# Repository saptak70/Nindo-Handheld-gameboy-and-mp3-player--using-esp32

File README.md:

# RetroHand — ESP32-S3 Retro Gaming + BT Audio Handheld

A custom handheld device built from scratch — PCB, firmware, 
and enclosure. Plays NES/DOOM, streams audio to BT headphones.

## Features
- ESP32-S3-WROOM-1 N8R8 (dual core, BT5, 8MB PSRAM)
- ST7789V3 1.69" 240×280 SPI display
- PCM5102A I2S DAC + 3.5mm jack + BT A2DP
- MicroSD for ROMs and music
- LiPo battery with TP4056 charging + DW01A protection
- Custom KiCad PCB + 3D printed enclosure

## Photos
[photos here]

## Hardware
[link to schematic PDF]
[link to BOM]

## Build Guide
[step by step]

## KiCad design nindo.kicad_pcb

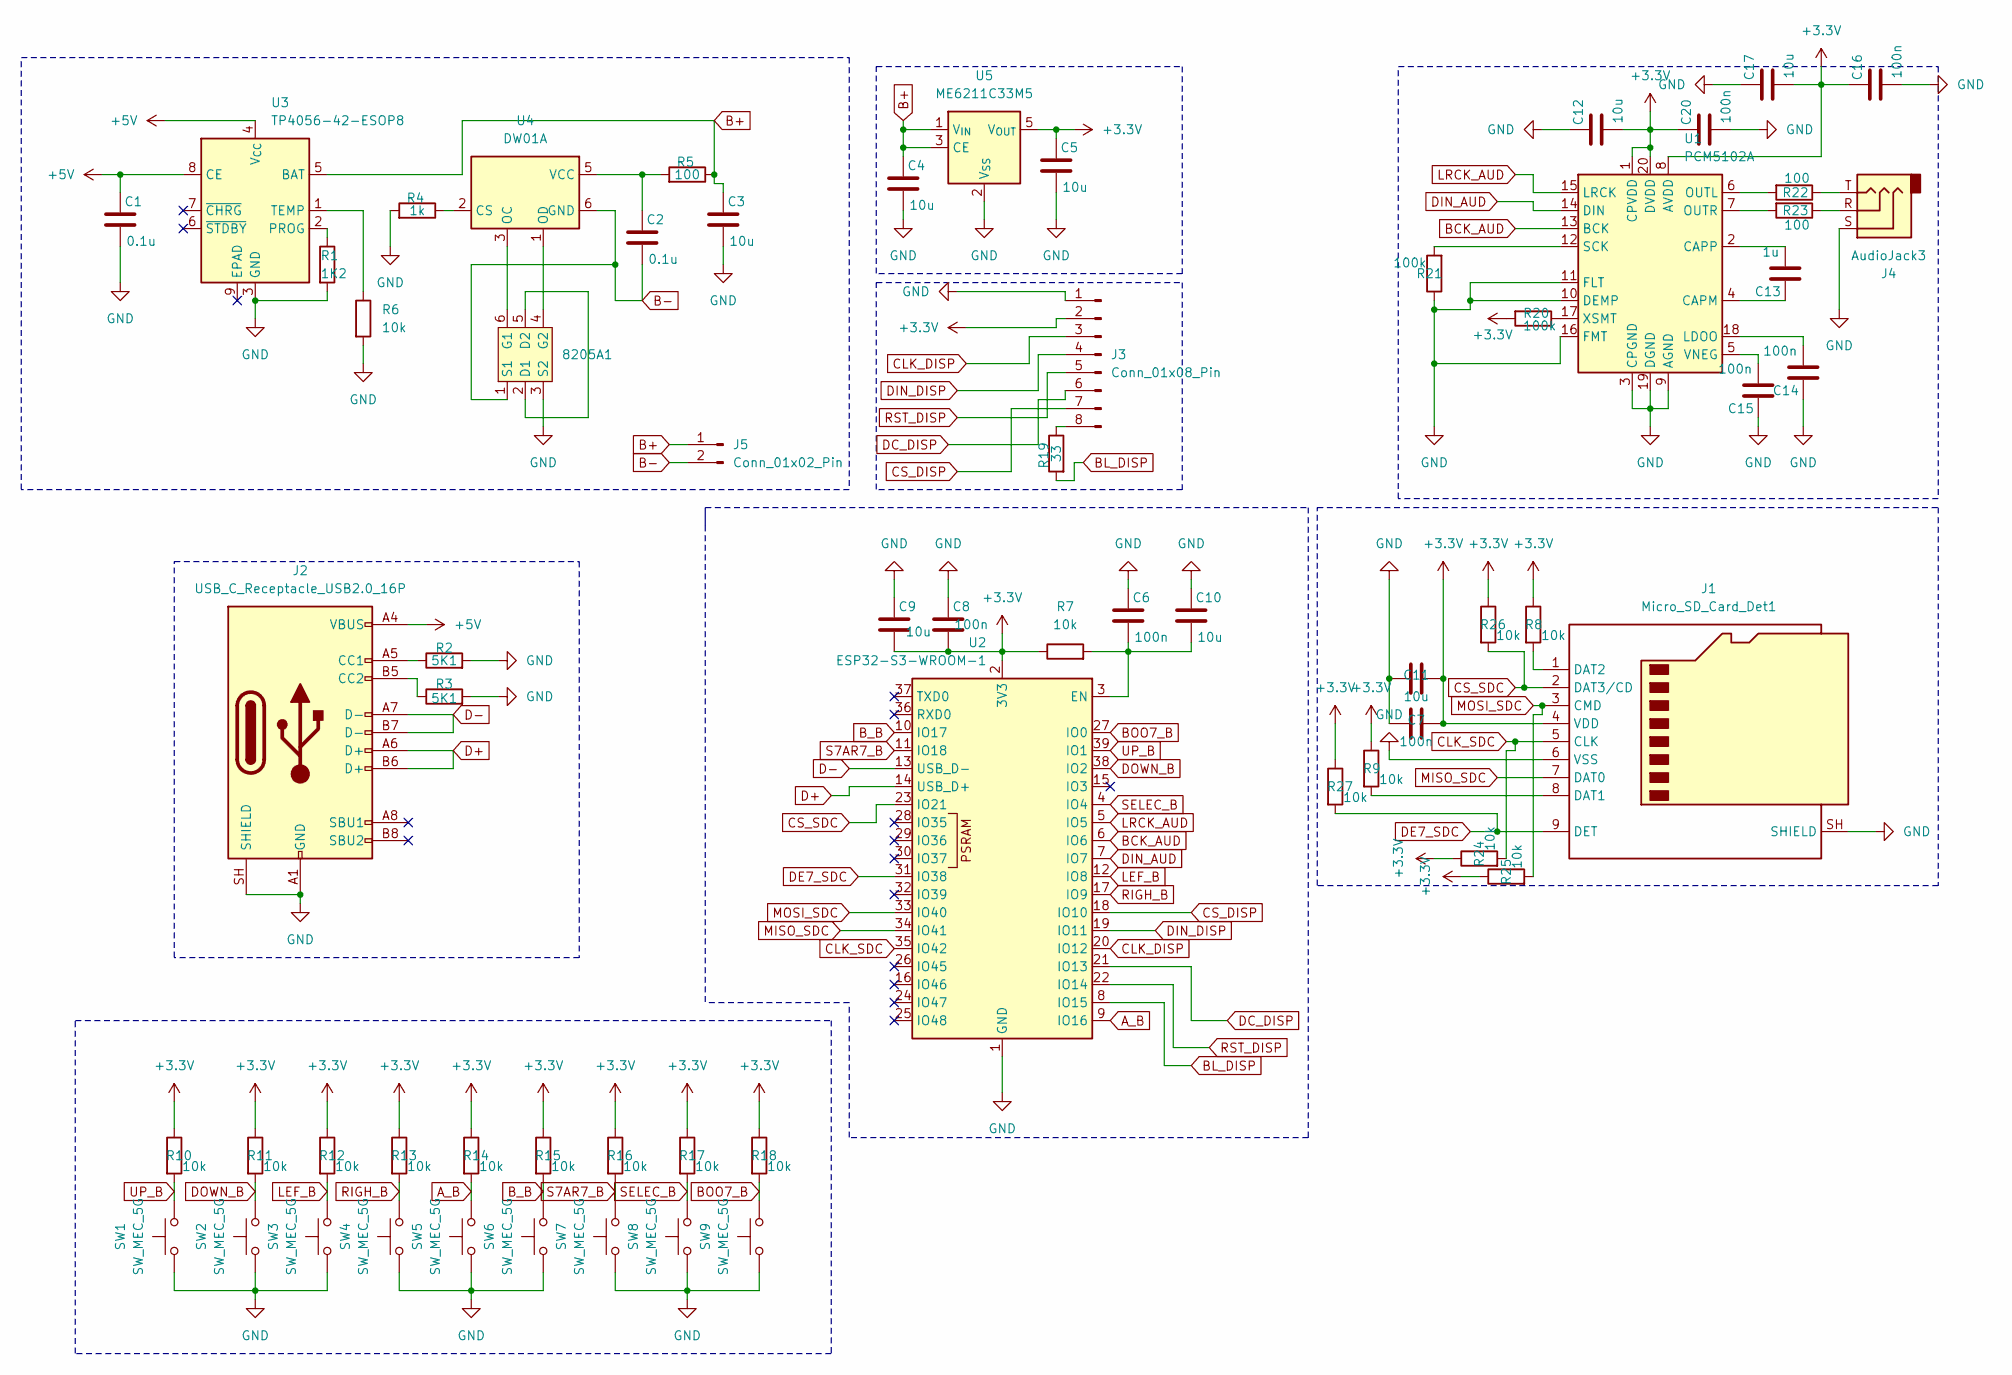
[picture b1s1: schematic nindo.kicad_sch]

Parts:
8205A1: SOT-23-6
C1, C2: 0.1u; C_1206_3216Metric_Pad1.33x1.80mm_HandSolder
C3, C4, C5, C9, C10, C11, C12, C17: 10u; C_1206_3216Metric_Pad1.33x1.80mm_HandSolder
C6, C7, C8, C14, C15, C16, C20: 100n; C_1206_3216Metric_Pad1.33x1.80mm_HandSolder
C13: 1u; C_1206_3216Metric_Pad1.33x1.80mm_HandSolder
J1: Micro_SD_Card_Det1; microSD_HC_Hirose_DM3AT-SF-PEJM5
J2: USB_C_Receptacle_USB2.0_16P; USB_C_Receptacle_G-Switch_GT-USB-7010ASV
J3: Conn_01x08_Pin; Harwin_M20-89008xx_1x08_P2.54mm_Horizontal
J4: AudioJack3; Jack_3.5mm_CUI_SJ1-3523N_Horizontal
J5: Conn_01x02_Pin; JWT_A3963_1x02_P3.96mm_Vertical
R1: 1K2; R_1206_3216Metric_Pad1.30x1.75mm_HandSolder
R2, R3: 5K1; R_1206_3216Metric_Pad1.30x1.75mm_HandSolder
R4: 1k; R_1206_3216Metric_Pad1.30x1.75mm_HandSolder
R5, R22, R23: 100; R_1206_3216Metric_Pad1.30x1.75mm_HandSolder
R6, R7, R8, R9, R10, R11, R12, R13, R14, R15, R16, R17, R18, R24, R25, R26, R27: 10k; R_1206_3216Metric_Pad1.30x1.75mm_HandSolder
R19: 33; R_1206_3216Metric_Pad1.30x1.75mm_HandSolder
R20, R21: 100k; R_1206_3216Metric_Pad1.30x1.75mm_HandSolder
SW1, SW2, SW3, SW4, SW5, SW6, SW7, SW8, SW9: SW_MEC_5G; SW_MEC_5GSH9
U1: PCM5102A; TSSOP-20_4.4x6.5mm_P0.65mm
U2: ESP32-S3-WROOM-1
U3: TP4056-42-ESOP8; SOIC-8-1EP_3.9x4.9mm_P1.27mm_EP2.41x3.3mm_ThermalVias
U4: DW01A; SOT-23-6
U5: ME6211C33M5; SOT-23-5

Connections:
+3.3V: C5.1, C7.2, C8.2, C9.2, C11.2, C12.2, C16.1, C17.2, C20.1, J1.4 (VDD), J3.2, R7.1, R8.1, R9.1, R10.1, R11.1, R12.1, R13.1, R14.1, R15.1, R16.1, R17.1, R18.1, R20.2, R24.1, R25.1, R26.1, R27.1, U1.1 (CPVDD), U1.8 (AVDD), U1.20 (DVDD), U2.2 (3V3), U5.5 (V_{OUT})
+5V: C1.1, J2.A4 (VBUS), J2.A9 (VBUS), J2.B4 (VBUS), J2.B9 (VBUS), U3.4 (V_{CC}), U3.8 (CE)
A_B: R14.2, SW5.3 (B), SW5.4 (B), U2.9 (IO16)
B+: C3.1, C4.1, J5.1, R5.1, U3.5 (BAT), U5.1 (V_{IN}), U5.3 (CE)
B-: 8205A1.1 (S1), C2.2, J5.2, U4.6 (GND)
BCK_AUD: U1.13 (BCK), U2.6 (IO6)
BL_DISP: R19.2, U2.8 (IO15)
BOO7_B: R18.2, SW9.3 (B), SW9.4 (B), U2.27 (IO0)
B_B: R15.2, SW6.3 (B), SW6.4 (B), U2.10 (IO17)
CLK_DISP: J3.3, U2.20 (IO12)
CLK_SDC: J1.5 (CLK), R24.2, U2.35 (IO42)
CS_DISP: J3.7, U2.18 (IO10)
CS_SDC: J1.2 (DAT3/CD), R26.2, U2.23 (IO21)
D+: J2.A6 (D+), J2.B6 (D+), U2.14 (USB_D+)
D-: J2.A7 (D-), J2.B7 (D-), U2.13 (USB_D-)
DC_DISP: J3.6, U2.21 (IO13)
DE7_SDC: J1.9 (DET), R27.2, U2.31 (IO38)
DIN_AUD: U1.14 (DIN), U2.7 (IO7)
DIN_DISP: J3.4, U2.19 (IO11)
DOWN_B: R11.2, SW2.3 (B), SW2.4 (B), U2.38 (IO2)
GND: 8205A1.3 (S2), C1.2, C3.2, C4.2, C5.2, C6.1, C7.1, C8.1, C9.1, C10.1, C11.1, C12.1, C14.1, C15.1, C16.2, C17.1, C20.2, J1.6 (VSS), J1.SH (SHIELD), J2.A1 (GND), J2.A12 (GND), J2.B1 (GND), J2.B12 (GND), J2.SH (SHIELD), J3.1, J4.S, R1.2, R2.2, R3.2, R4.2, R6.2, R21.1, SW1.1 (A), SW1.2 (A), SW2.1 (A), SW2.2 (A), SW3.1 (A), SW3.2 (A), SW4.1 (A), SW4.2 (A), SW5.1 (A), SW5.2 (A), SW6.1 (A), SW6.2 (A), SW7.1 (A), SW7.2 (A), SW8.1 (A), SW8.2 (A), SW9.1 (A), SW9.2 (A), U1.3 (CPGND), U1.9 (AGND), U1.10 (DEMP), U1.11 (FLT), U1.16 (FMT), U1.19 (DGND), U2.1 (GND), U2.40 (GND), U2.41 (GND), U3.3 (GND), U5.2 (V_{SS})
LEF_B: R12.2, SW3.3 (B), SW3.4 (B), U2.12 (IO8)
LRCK_AUD: U1.15 (LRCK), U2.5 (IO5)
MISO_SDC: J1.7 (DAT0), U2.34 (IO41)
MOSI_SDC: J1.3 (CMD), R25.2, U2.33 (IO40)
unnamed: 8205A1.2 (D1), 8205A1.5 (D2)
unnamed: 8205A1.6 (G1), U4.3 (OC)
unnamed: 8205A1.4 (G2), U4.1 (OD)
unnamed: J1.8 (DAT1), R9.2
unnamed: J1.1 (DAT2), R8.2
unnamed: J2.A5 (CC1), R2.1
unnamed: J2.B5 (CC2), R3.1
unnamed: J3.8, R19.1
unnamed: J4.R, R23.1
unnamed: J4.T, R22.1
unnamed: C13.1, U1.4 (CAPM)
unnamed: C13.2, U1.2 (CAPP)
unnamed: C14.2, U1.18 (LDOO)
unnamed: R22.2, U1.6 (OUTL)
unnamed: R23.2, U1.7 (OUTR)
unnamed: R21.2, U1.12 (SCK)
unnamed: C15.2, U1.5 (VNEG)
unnamed: R20.1, U1.17 (XSMT)
unnamed: C6.2, C10.2, R7.2, U2.3 (EN)
unnamed: R1.1, U3.2 (PROG)
unnamed: R6.1, U3.1 (TEMP)
unnamed: R4.1, U4.2 (CS)
unnamed: C2.1, R5.2, U4.5 (VCC)
RIGH_B: R13.2, SW4.3 (B), SW4.4 (B), U2.17 (IO9)
RST_DISP: J3.5, U2.22 (IO14)
S7AR7_B: R16.2, SW7.3 (B), SW7.4 (B), U2.11 (IO18)
SELEC_B: R17.2, SW8.3 (B), SW8.4 (B), U2.4 (IO4)
UP_B: R10.2, SW1.3 (B), SW1.4 (B), U2.39 (IO1)

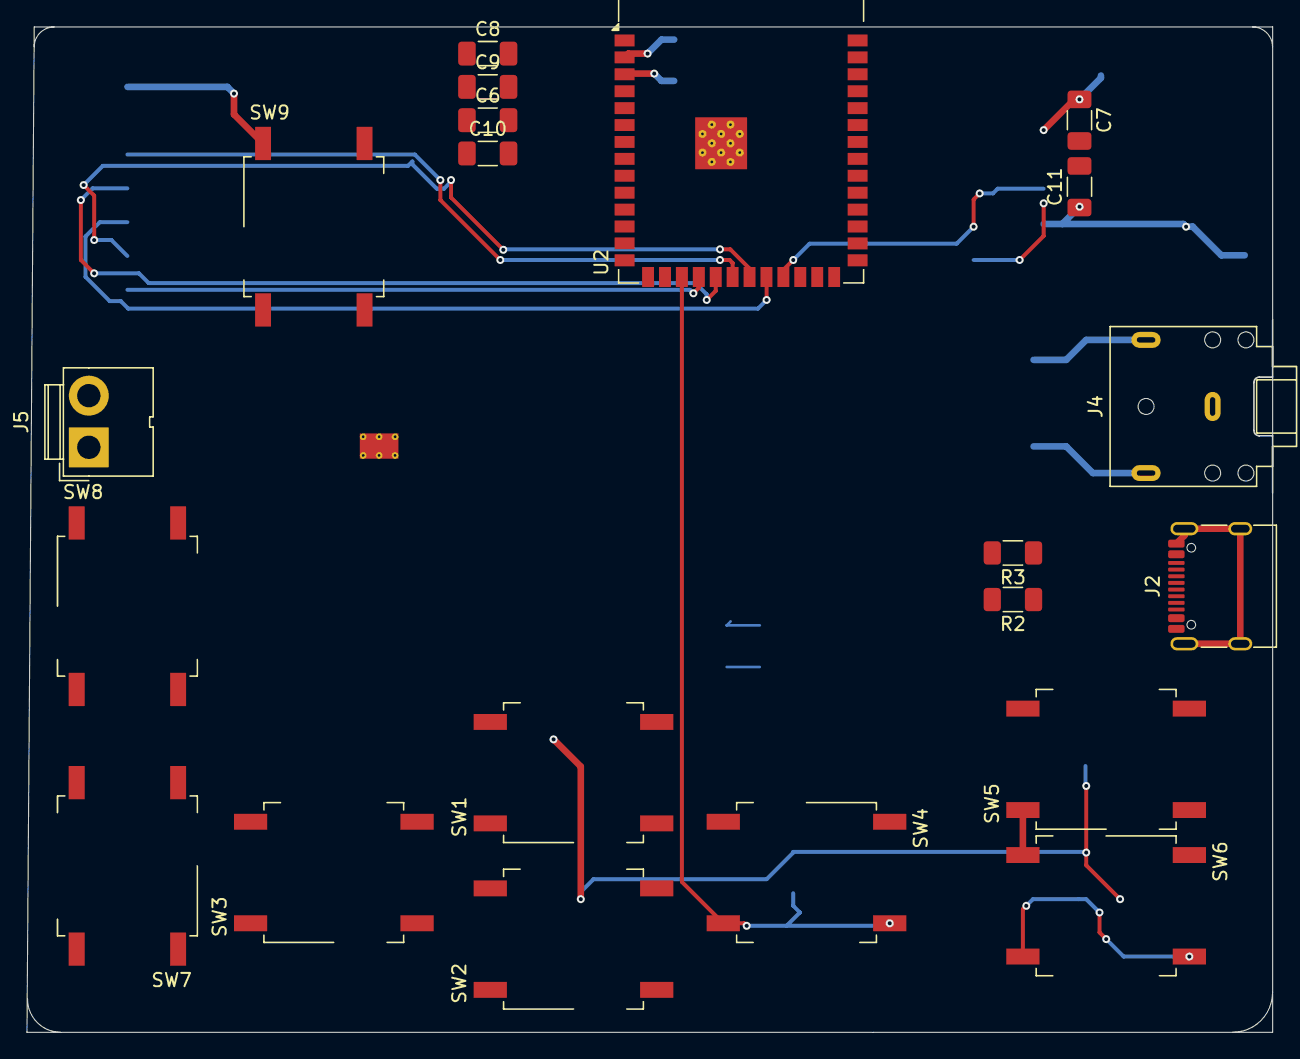
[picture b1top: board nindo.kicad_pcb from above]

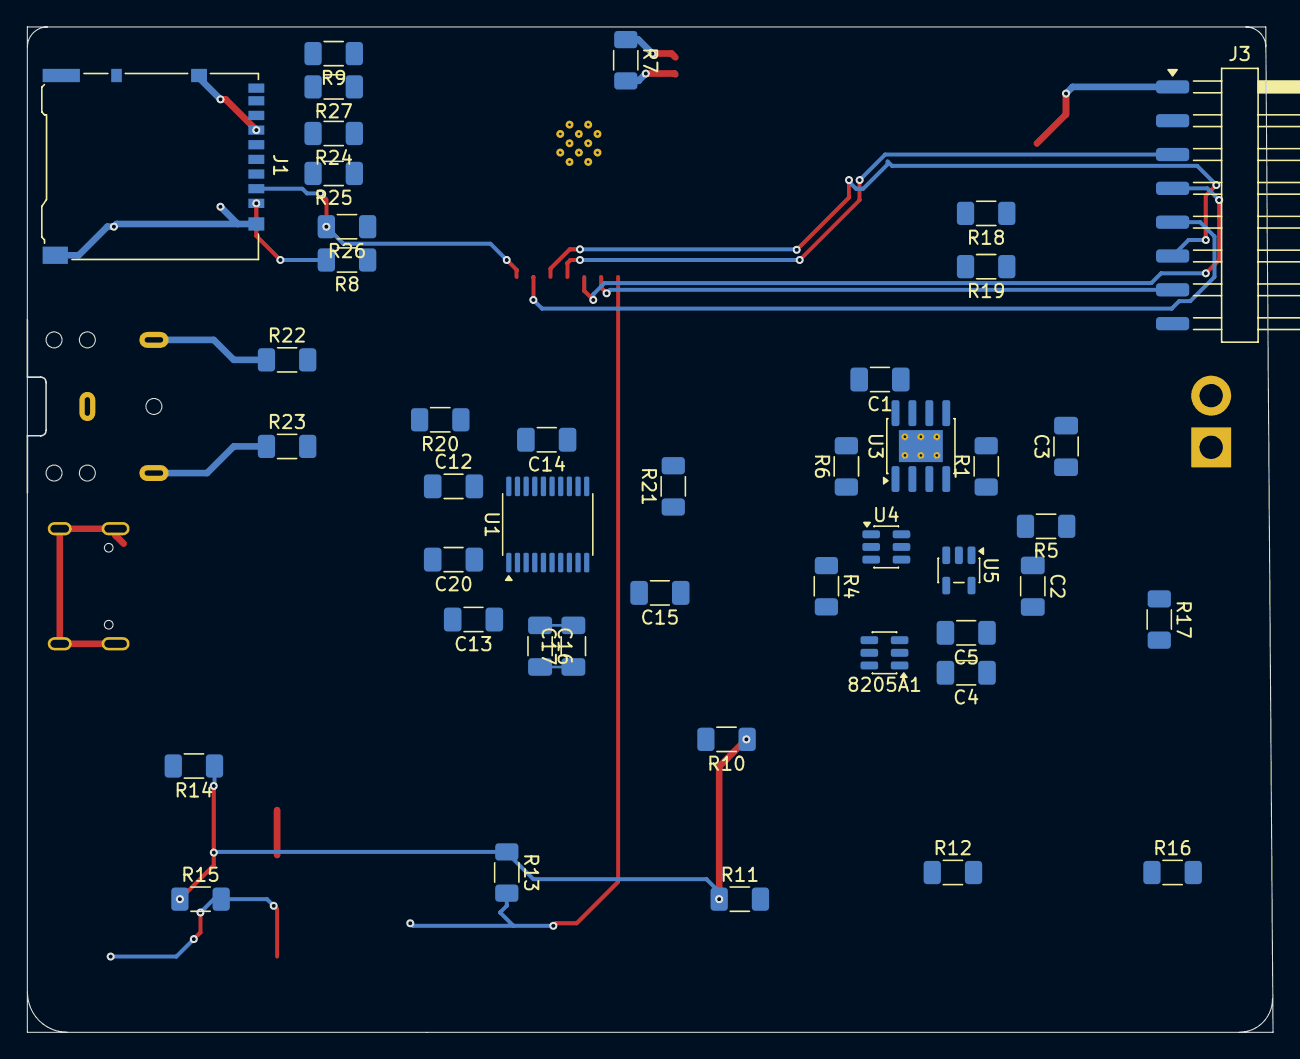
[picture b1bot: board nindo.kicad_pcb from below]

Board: 2 copper layers, 93.5 x 75.4 mm, 65 parts (44 on the bottom side), 53 nets.

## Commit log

2026-05-10 uploaded schematic
2026-05-10 readme
2026-05-31 hhhh
2026-05-31 pdf schema
